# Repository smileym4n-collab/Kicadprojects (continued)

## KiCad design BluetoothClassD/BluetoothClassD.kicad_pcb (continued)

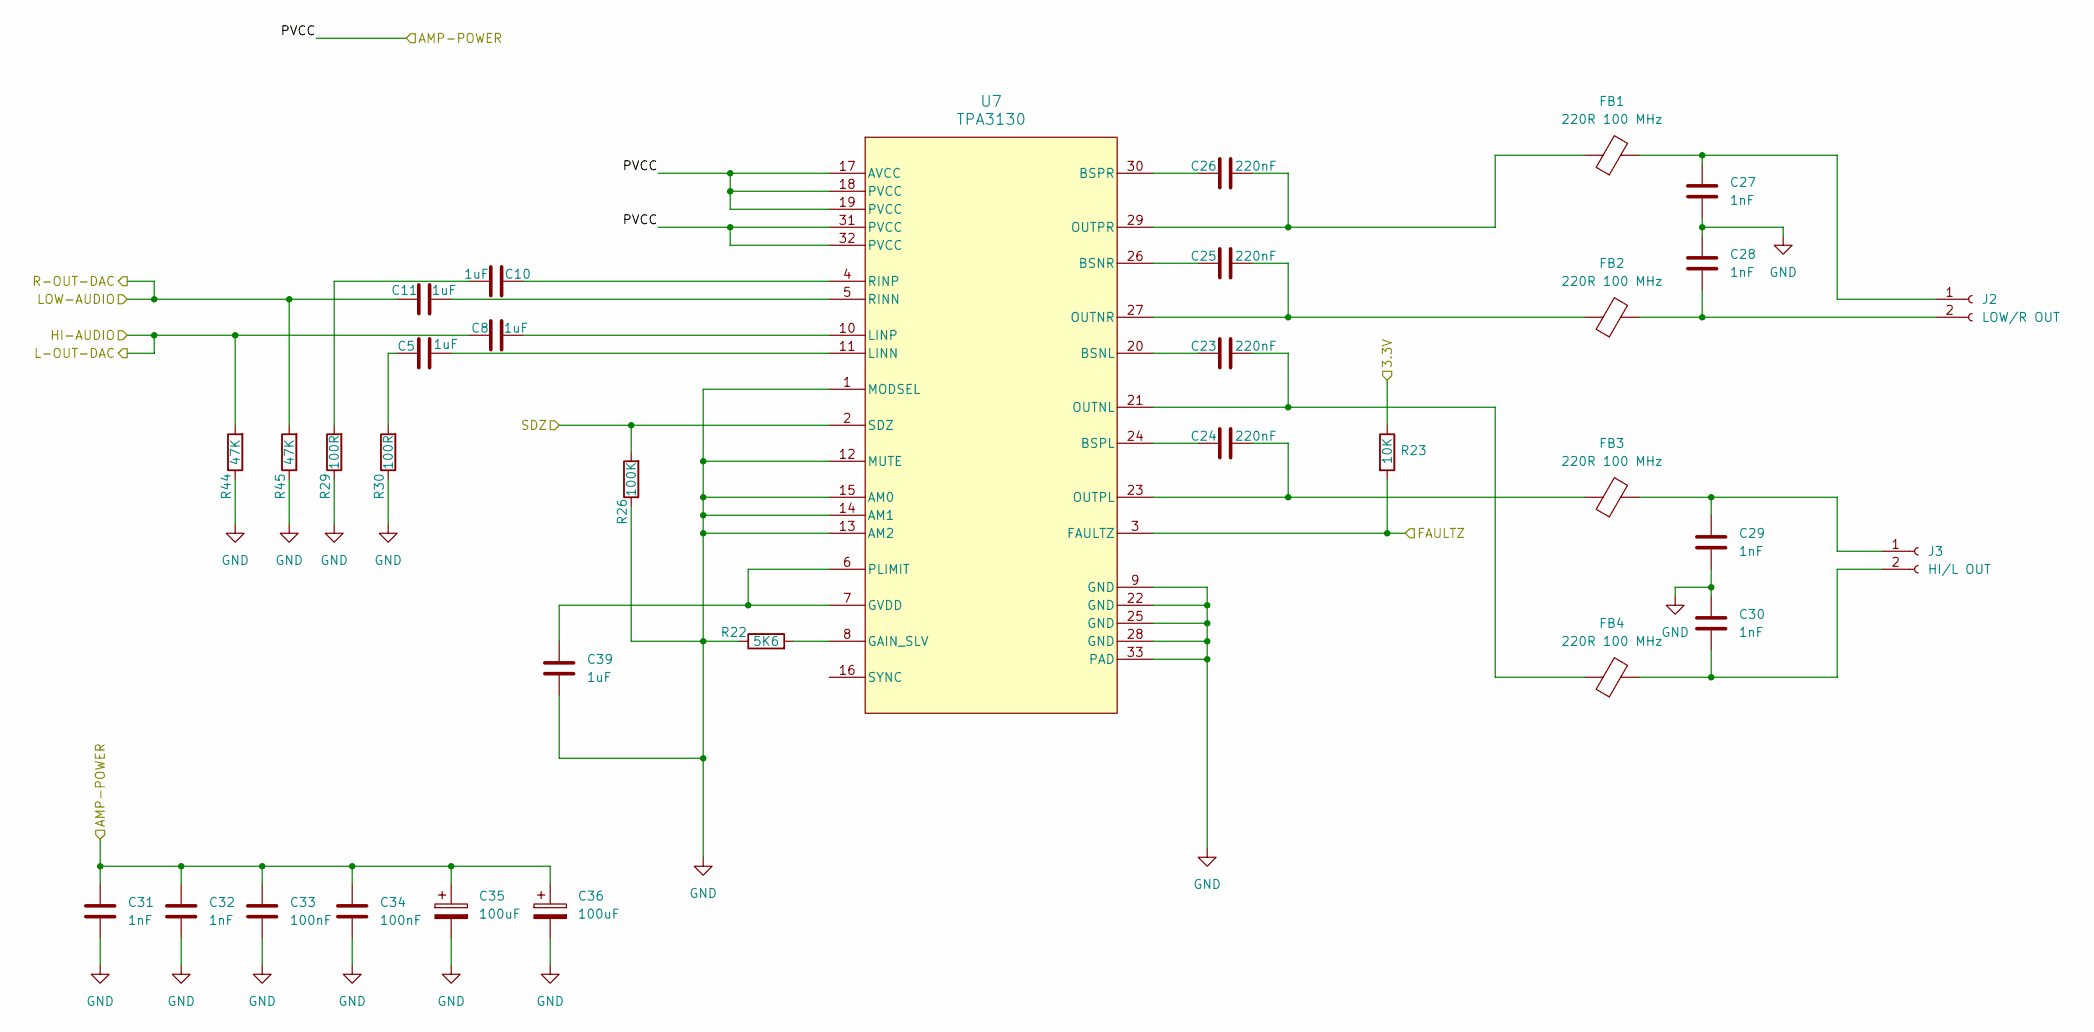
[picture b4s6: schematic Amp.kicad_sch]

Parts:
C5, C8, C10, C11: 1uF; C_Rect_L7.2mm_W5.5mm_P5.00mm_FKS2_FKP2_MKS2_MKP2
C23, C24, C25, C26: 220nF; C_0805_2012Metric_Pad1.18x1.45mm_HandSolder
C27, C28, C29, C30: 1nF; C_0805_2012Metric_Pad1.18x1.45mm_HandSolder
C31, C32: 1nF; C_0603_1608Metric_Pad1.08x0.95mm_HandSolder
C33, C34: 100nF; C_1206_3216Metric_Pad1.33x1.80mm_HandSolder
C35, C36: 100uF; CP_Radial_D8.0mm_P3.50mm
C39: 1uF; C_1206_3216Metric_Pad1.33x1.80mm_HandSolder
FB1, FB2, FB3, FB4: 220R 100 MHz; L_1206_3216Metric_Pad1.22x1.90mm_HandSolder
J2: LOW/R OUT; JST_XH_B2B-XH-A_1x02_P2.50mm_Vertical
J3: HI/L OUT; JST_XH_B2B-XH-A_1x02_P2.50mm_Vertical
R22: 5K6; R_0805_2012Metric_Pad1.20x1.40mm_HandSolder
R23: 10K; R_0805_2012Metric_Pad1.20x1.40mm_HandSolder
R26: 100K; R_0805_2012Metric_Pad1.20x1.40mm_HandSolder
R29, R30: 100R; R_0805_2012Metric_Pad1.20x1.40mm_HandSolder
R44, R45: 47K; R_0805_2012Metric_Pad1.20x1.40mm_HandSolder
U7: TPA3130; TPA3130D2DAPR

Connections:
/Amp/FAULTZ: R23.2, U7.3 (FAULTZ); also elsewhere on the board
/Amp/HI-AUDIO: C8.1, R44.2; also elsewhere on the board
/Amp/LOW-AUDIO: C11.1, R45.2; also elsewhere on the board
/Amp/PVCC: C31.1, C32.1, C33.1, C34.1, C35.1, C36.1, U7.17 (AVCC), U7.18 (PVCC), U7.19 (PVCC), U7.31 (PVCC), U7.32 (PVCC); also elsewhere on the board
/Amp/SDZ: R26.2, U7.2 (SDZ); also elsewhere on the board
/ESP-3V3: R23.1; also elsewhere on the board
GND: C27.2, C28.1, C29.2, C30.1, C31.2, C32.2, C33.2, C34.2, C35.2, C36.2, C39.2, R22.1, R26.1, R29.1, R30.1, R44.1, R45.1, U7.1 (MODSEL), U7.9 (GND), U7.12 (MUTE), U7.13 (AM2), U7.14 (AM1), U7.15 (AM0), U7.22 (GND), U7.25 (GND), U7.28 (GND), U7.33 (PAD); also elsewhere on the board
unnamed: C5.1, R30.2
unnamed: C10.1, R29.2
unnamed: C27.1, FB1.2, J2.1
unnamed: C28.2, FB2.2, J2.2
unnamed: C29.1, FB3.2, J3.1
unnamed: C30.2, FB4.2, J3.2
unnamed: C23.1, U7.20 (BSNL)
unnamed: C25.1, U7.26 (BSNR)
unnamed: C24.1, U7.24 (BSPL)
unnamed: C26.1, U7.30 (BSPR)
unnamed: R22.2, U7.8 (GAIN_SLV)
unnamed: C39.1, U7.6 (PLIMIT), U7.7 (GVDD)
unnamed: C5.2, U7.11 (LINN)
unnamed: C8.2, U7.10 (LINP)
unnamed: C23.2, FB4.1, U7.21 (OUTNL)
unnamed: C25.2, FB2.1, U7.27 (OUTNR)
unnamed: C24.2, FB3.1, U7.23 (OUTPL)
unnamed: C26.2, FB1.1, U7.29 (OUTPR)
unnamed: C11.2, U7.5 (RINN)
unnamed: C10.2, U7.4 (RINP)

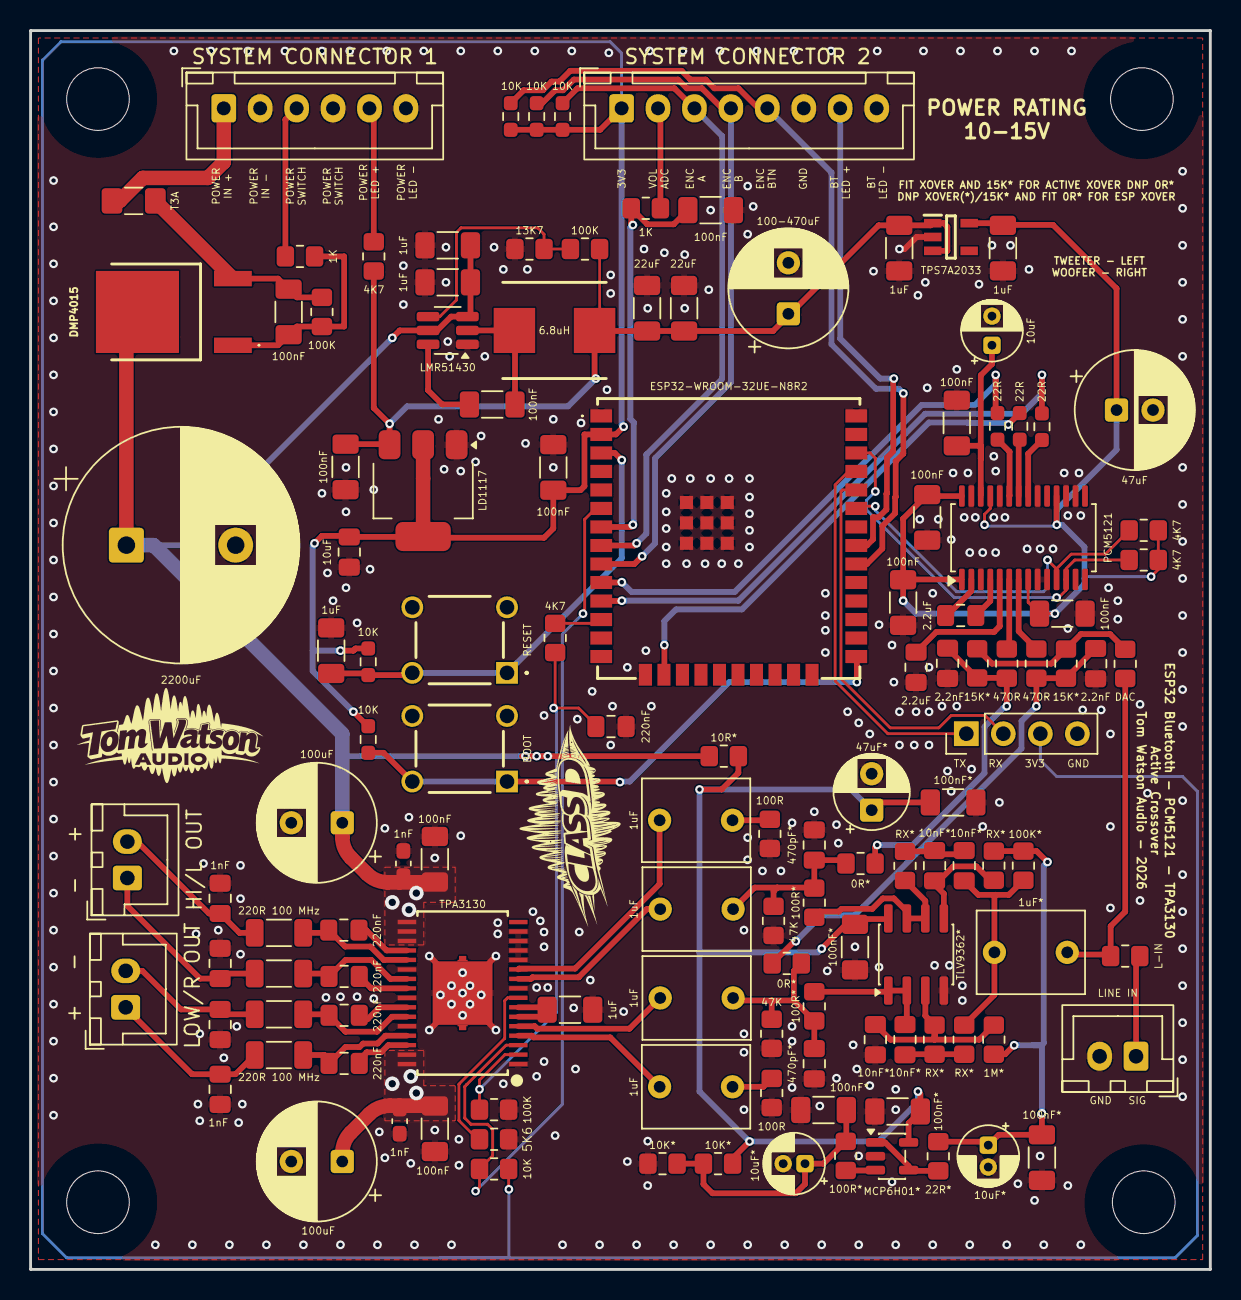
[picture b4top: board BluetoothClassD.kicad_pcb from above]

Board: 2 copper layers, 81.0 x 85.0 mm, 132 parts (0 on the bottom side), 79 nets.

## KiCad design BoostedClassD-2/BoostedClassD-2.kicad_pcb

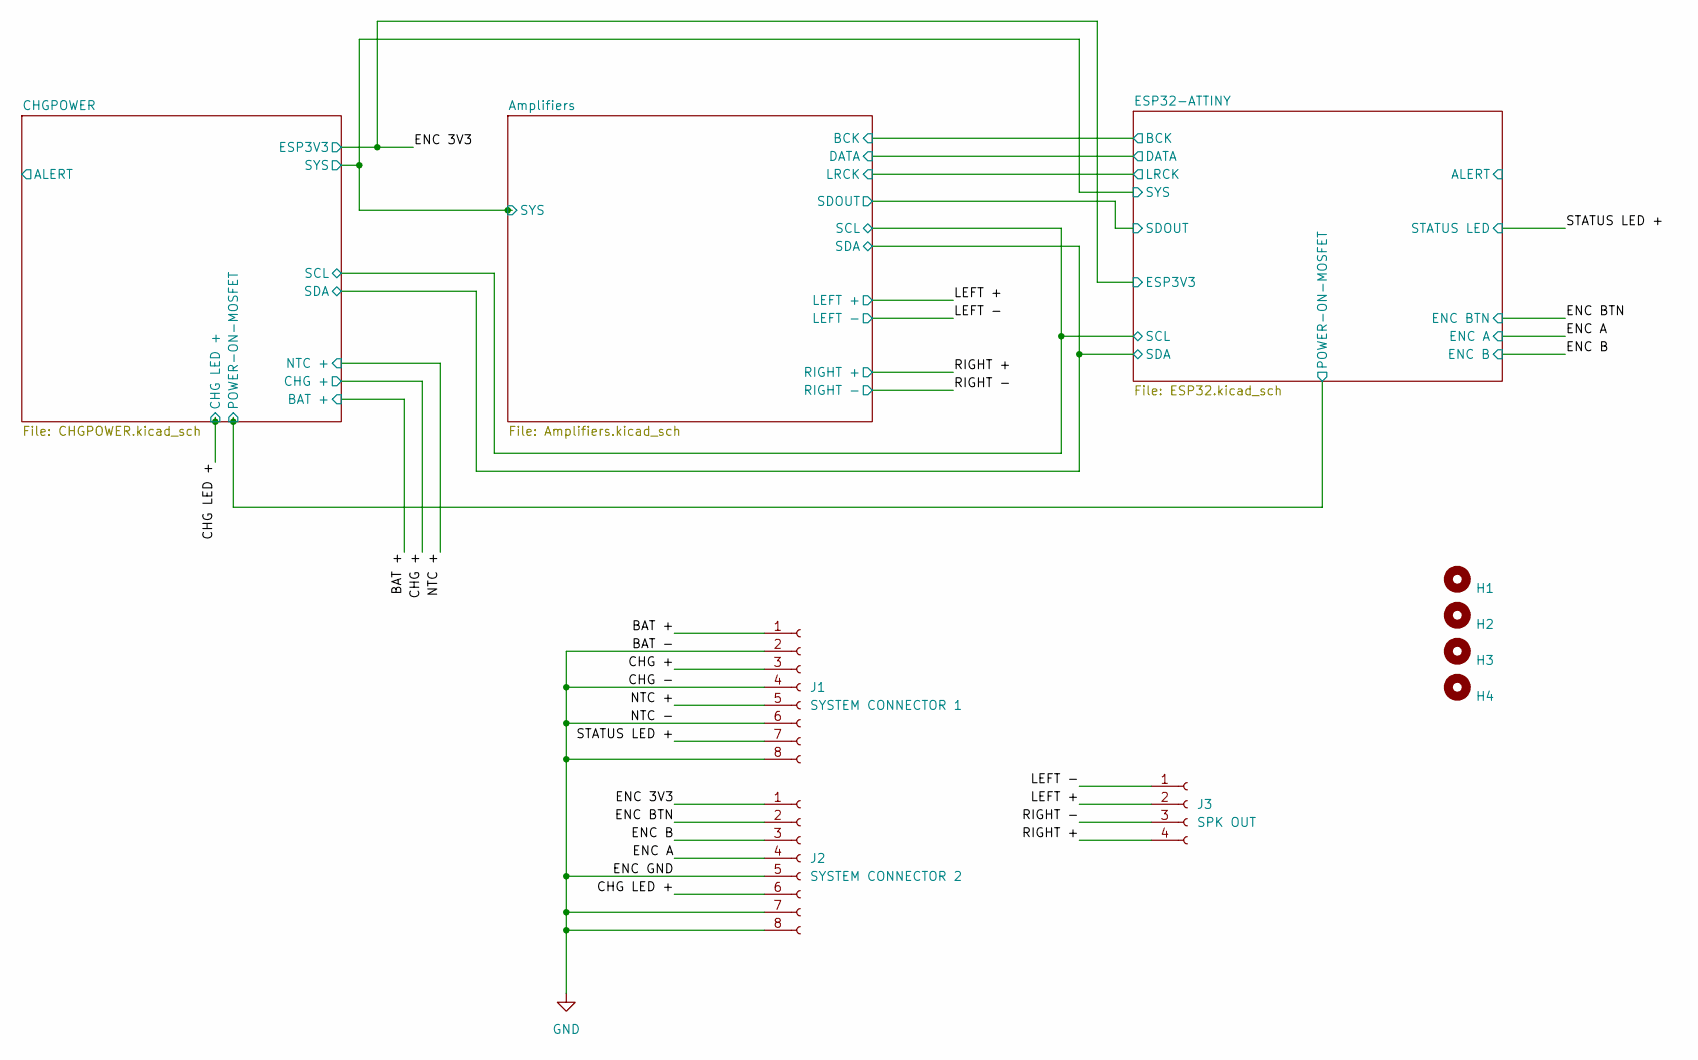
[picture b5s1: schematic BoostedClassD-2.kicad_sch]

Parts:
H1, H2, H3, H4: MountingHole_4.3mm_M4
J1: SYSTEM CONNECTOR 1; JST_XH_B8B-XH-A_1x08_P2.50mm_Vertical
J2: SYSTEM CONNECTOR 2; JST_XH_B8B-XH-A_1x08_P2.50mm_Vertical
J3: SPK OUT; JST_XH_B4B-XH-A_1x04_P2.50mm_Vertical

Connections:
/BAT +: J1.1; also elsewhere on the board
/CHG +: J1.3; also elsewhere on the board
/CHG LED +: J2.6; also elsewhere on the board
/ENC 3V3: J2.1; also elsewhere on the board
/ENC A: J2.4; also elsewhere on the board
/ENC B: J2.3; also elsewhere on the board
/ENC BTN: J2.2; also elsewhere on the board
/LEFT +: J3.2; also elsewhere on the board
/LEFT -: J3.1; also elsewhere on the board
/NTC +: J1.5; also elsewhere on the board
/RIGHT +: J3.4; also elsewhere on the board
/RIGHT -: J3.3; also elsewhere on the board
/STATUS LED +: J1.7; also elsewhere on the board
GND: J1.2, J1.4, J1.6, J1.8, J2.5, J2.7, J2.8; also elsewhere on the board

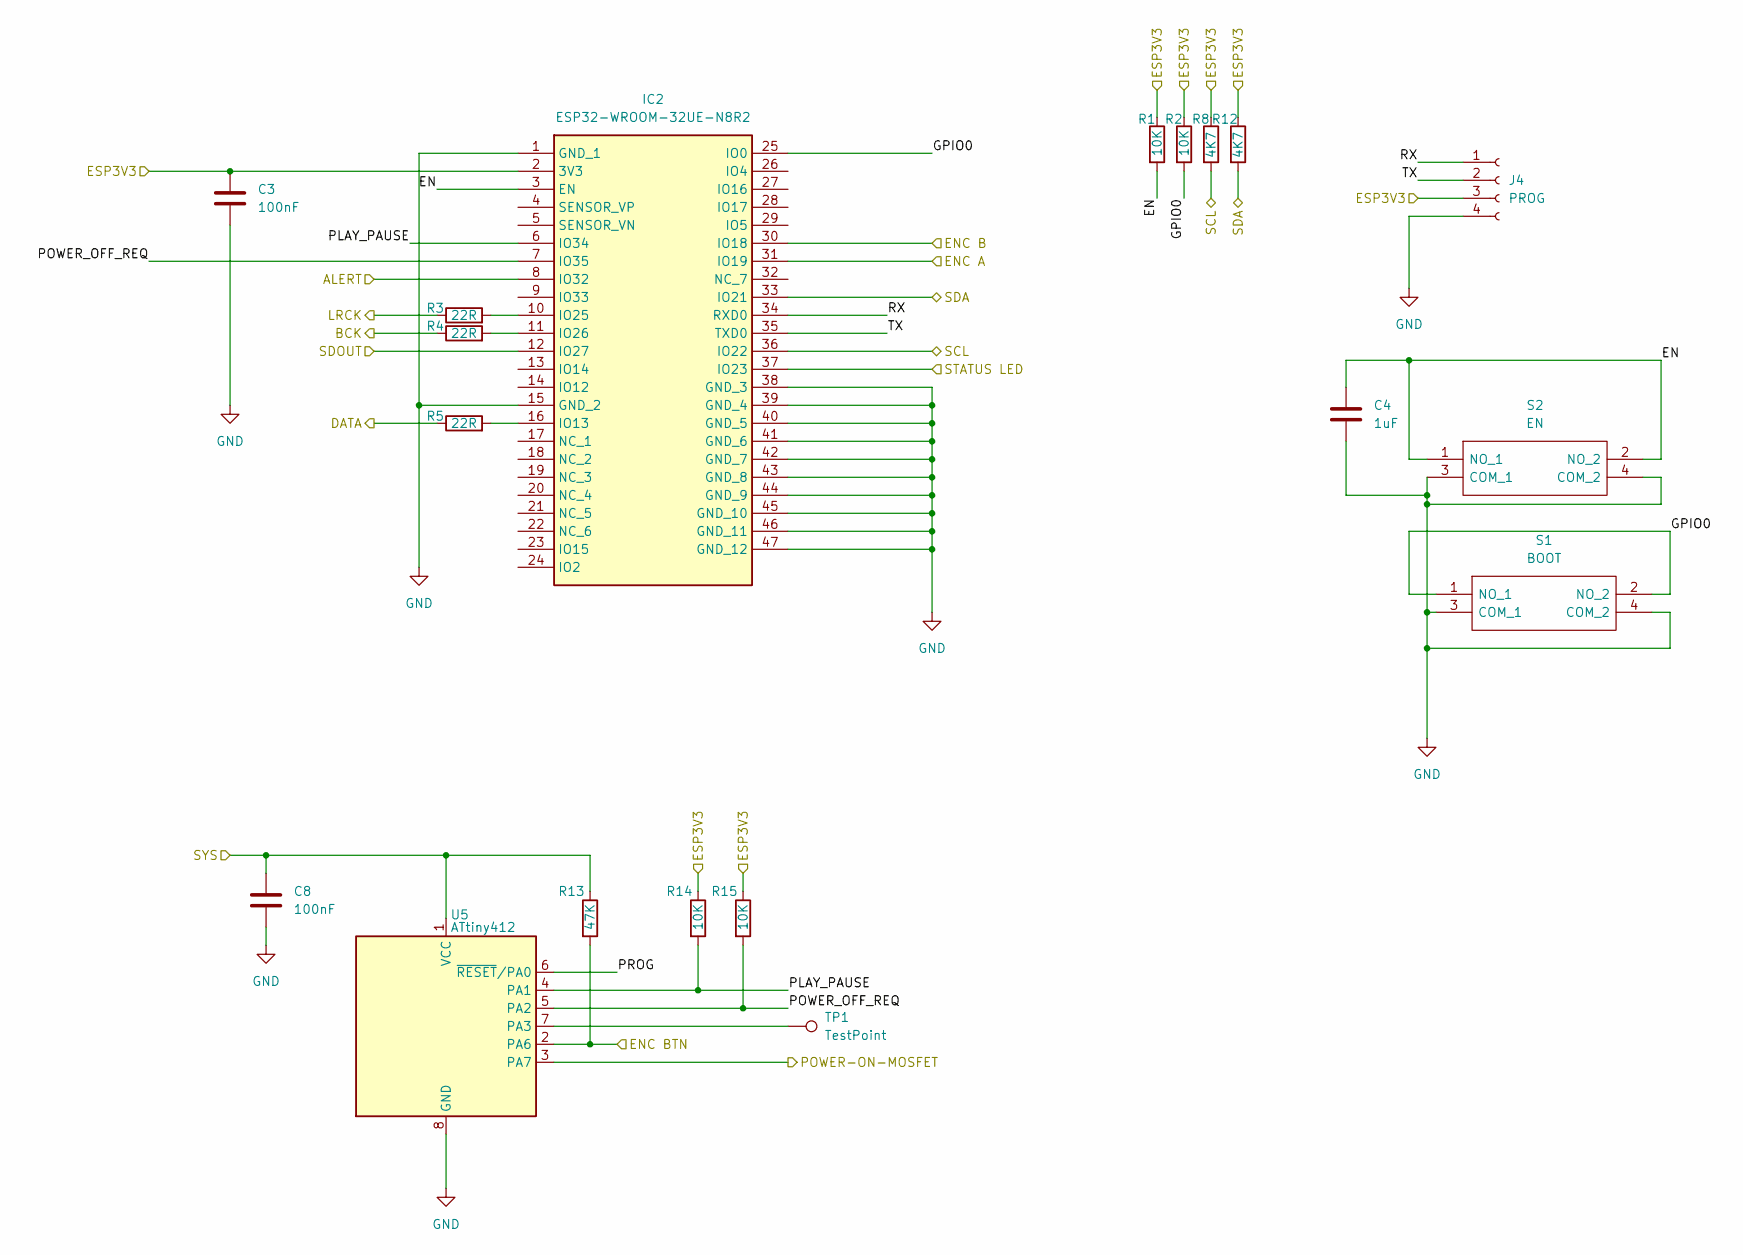
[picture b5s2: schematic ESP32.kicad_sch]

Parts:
C3, C8: 100nF; C_1206_3216Metric_Pad1.33x1.80mm_HandSolder
C4: 1uF; C_1206_3216Metric_Pad1.33x1.80mm_HandSolder
IC2: ESP32-WROOM-32UE-N8R2; ESP32WROOM32UEN8R2; Mouser Part Number 356-ESP32WRM32UEN8R2
J4: PROG; PinHeader_1x04_P2.54mm_Vertical
R1, R2: 10K; R_0603_1608Metric_Pad0.98x0.95mm_HandSolder
R3, R4, R5: 22R; R_0603_1608Metric_Pad0.98x0.95mm_HandSolder
R8, R12: 4K7; R_0805_2012Metric_Pad1.20x1.40mm_HandSolder
R13: 47K; R_0805_2012Metric_Pad1.20x1.40mm_HandSolder
R14, R15: 10K; R_0805_2012Metric_Pad1.20x1.40mm_HandSolder
S1: BOOT; PTS810SJM250SMTRLFS; Mouser Part Number 611-PTS810SJM250SMTR
S2: EN; PTS810SJM250SMTRLFS; Mouser Part Number 611-PTS810SJM250SMTR
TP1: TestPoint; TestPoint_Pad_D2.0mm
U5: ATtiny412; SOIC-8_3.9x4.9mm_P1.27mm

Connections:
/Amplifiers/BCK: R4.1; also elsewhere on the board
/Amplifiers/DATA: R5.1; also elsewhere on the board
/Amplifiers/LRCK: R3.1; also elsewhere on the board
/Amplifiers/SCL: IC2.36 (IO22), R8.2; also elsewhere on the board
/Amplifiers/SDA: IC2.33 (IO21), R12.2; also elsewhere on the board
/Amplifiers/SDOUT: IC2.12 (IO27)
/Amplifiers/SYS: C8.1, R13.1, U5.1 (VCC); also elsewhere on the board
/CHGPOWER/POWER-ON-MOSFET: U5.3 (PA7); also elsewhere on the board
/ENC 3V3: C3.1, IC2.2 (3V3), J4.3, R1.1, R2.1, R8.1, R12.1, R14.1, R15.1; also elsewhere on the board
/ENC A: IC2.31 (IO19); also elsewhere on the board
/ENC B: IC2.30 (IO18); also elsewhere on the board
/ENC BTN: R13.2, U5.2 (PA6); also elsewhere on the board
/ESP32-ATTINY/ALERT: IC2.8 (IO32)
/ESP32-ATTINY/EN: C4.1, IC2.3 (EN), R1.2, S2.1 (NO_1), S2.2 (NO_2)
/ESP32-ATTINY/GPIO0: IC2.25 (IO0), R2.2, S1.1 (NO_1), S1.2 (NO_2)
/ESP32-ATTINY/PLAY_PAUSE: IC2.6 (IO34), R14.2, U5.4 (PA1)
/ESP32-ATTINY/POWER_OFF_REQ: IC2.7 (IO35), R15.2, U5.5 (PA2)
/ESP32-ATTINY/PROG: U5.6 (~RESET/PA0)
/ESP32-ATTINY/RX: IC2.34 (RXD0), J4.1
/ESP32-ATTINY/TX: IC2.35 (TXD0), J4.2
/STATUS LED +: IC2.37 (IO23); also elsewhere on the board
GND: C3.2, C4.2, C8.2, IC2.1 (GND_1), IC2.15 (GND_2), IC2.38 (GND_3), IC2.39 (GND_4), IC2.40 (GND_5), IC2.41 (GND_6), IC2.42 (GND_7), IC2.43 (GND_8), IC2.44 (GND_9), IC2.45 (GND_10), IC2.46 (GND_11), IC2.47 (GND_12), J4.4, S1.3 (COM_1), S1.4 (COM_2), S2.3 (COM_1), S2.4 (COM_2), U5.8 (GND); also elsewhere on the board
unnamed: IC2.16 (IO13), R5.2
unnamed: IC2.10 (IO25), R3.2
unnamed: IC2.11 (IO26), R4.2
unnamed: TP1.1 (1_1), U5.7 (PA3)

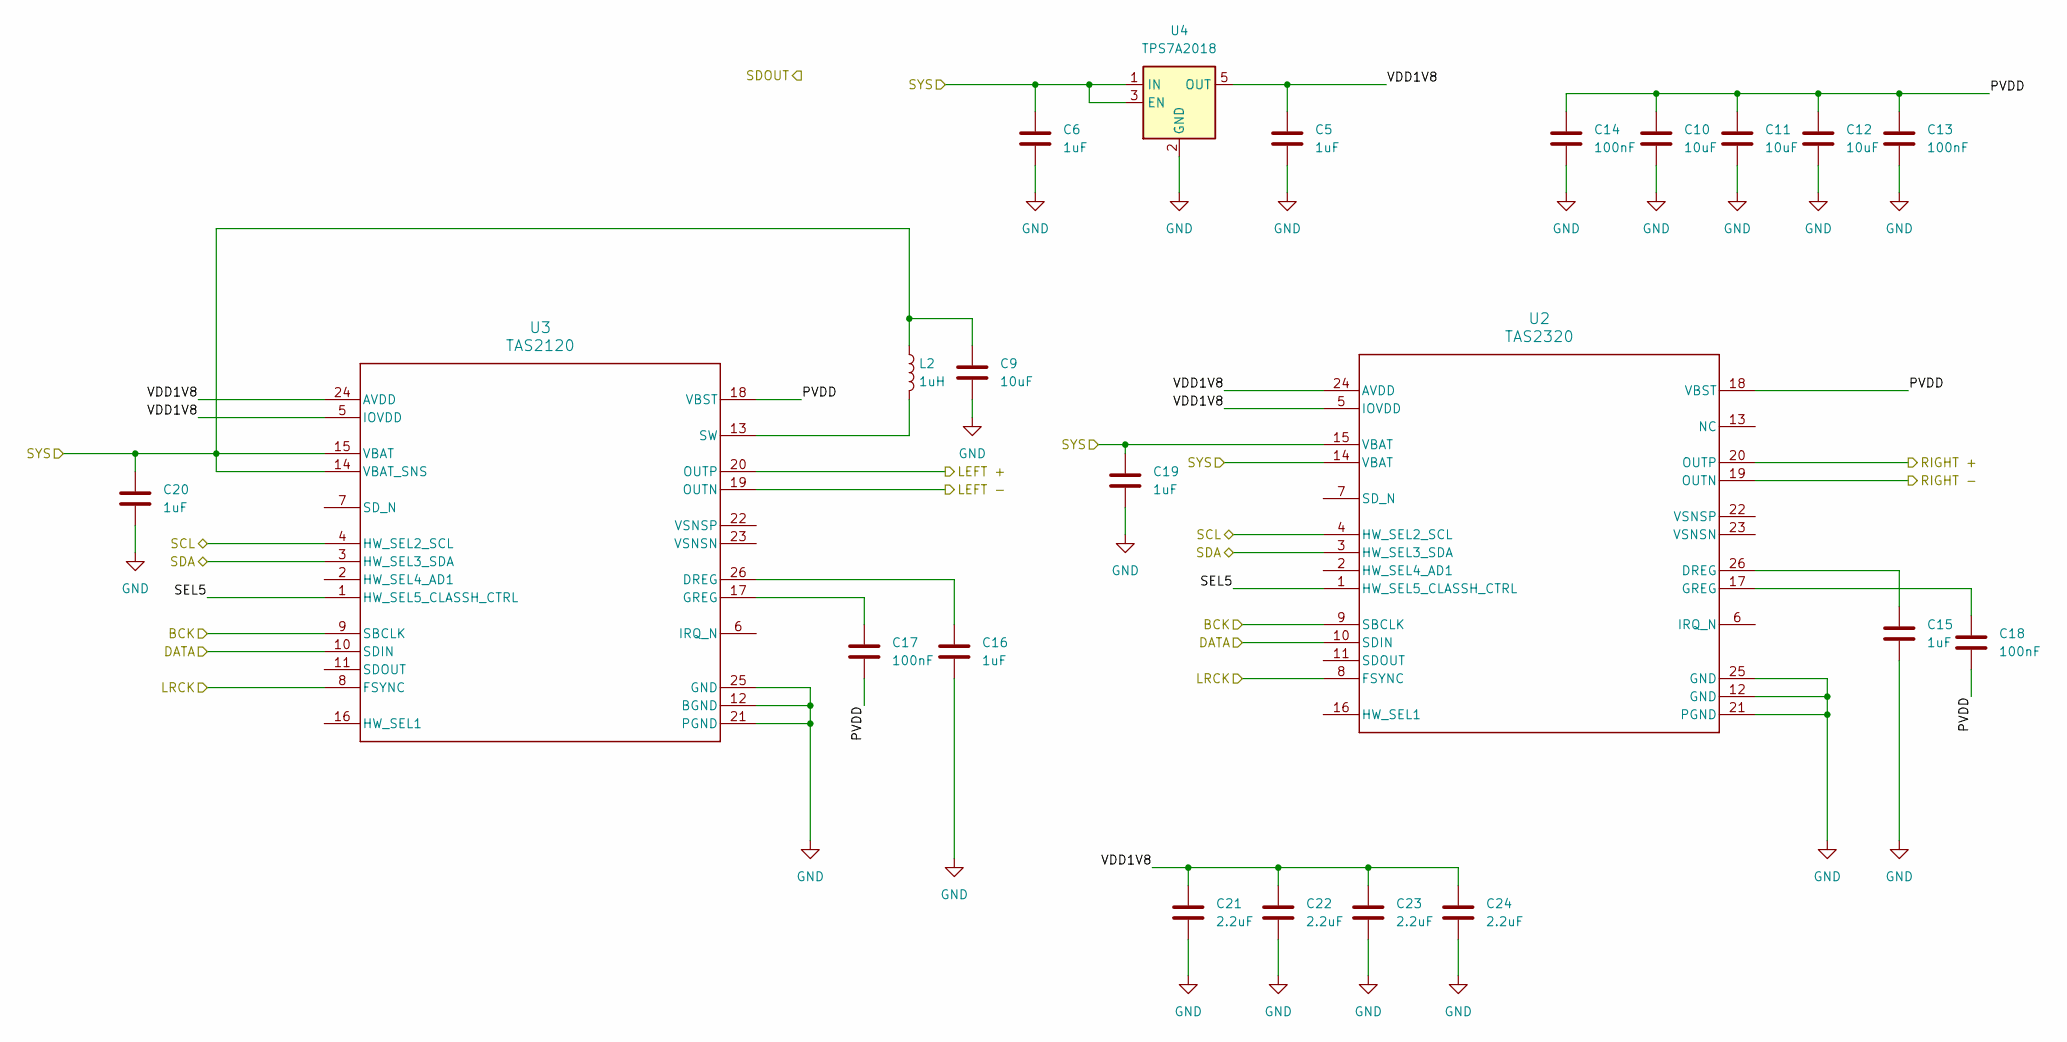
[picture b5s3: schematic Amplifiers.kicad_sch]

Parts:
C5, C6, C15, C16, C19, C20: 1uF; C_1206_3216Metric_Pad1.33x1.80mm_HandSolder
C9, C10, C11, C12: 10uF; C_1206_3216Metric_Pad1.33x1.80mm_HandSolder
C13, C14, C17, C18: 100nF; C_1206_3216Metric_Pad1.33x1.80mm_HandSolder
C21, C22, C23, C24: 2.2uF; C_0805_2012Metric_Pad1.18x1.45mm_HandSolder
L2: 1uH; L_1008_2520Metric_Pad1.43x2.20mm_HandSolder
U2: TAS2320; TAS2120
U3: TAS2120
U4: TPS7A2018; SOT-23-5

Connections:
/Amplifiers/BCK: U2.9 (SBCLK), U3.9 (SBCLK); also elsewhere on the board
/Amplifiers/DATA: U2.10 (SDIN), U3.10 (SDIN); also elsewhere on the board
/Amplifiers/LRCK: U2.8 (FSYNC), U3.8 (FSYNC); also elsewhere on the board
/Amplifiers/PVDD: C10.1, C11.1, C12.1, C13.1, C14.1, C17.2, C18.2, U2.18 (VBST), U3.18 (VBST)
/Amplifiers/SCL: U2.4 (HW_SEL2_SCL), U3.4 (HW_SEL2_SCL); also elsewhere on the board
/Amplifiers/SDA: U2.3 (HW_SEL3_SDA), U3.3 (HW_SEL3_SDA); also elsewhere on the board
/Amplifiers/SEL5: U2.1 (HW_SEL5_CLASSH_CTRL), U3.1 (HW_SEL5_CLASSH_CTRL)
/Amplifiers/SYS: C6.1, C9.1, C19.1, C20.1, L2.1, U2.14 (VBAT), U2.15 (VBAT), U3.14 (VBAT_SNS), U3.15 (VBAT), U4.1 (IN), U4.3 (EN); also elsewhere on the board
/Amplifiers/VDD1V8: C5.1, C21.1, C22.1, C23.1, C24.1, U2.5 (IOVDD), U2.24 (AVDD), U3.5 (IOVDD), U3.24 (AVDD), U4.5 (OUT)
/LEFT +: U3.20 (OUTP); also elsewhere on the board
/LEFT -: U3.19 (OUTN); also elsewhere on the board
/RIGHT +: U2.20 (OUTP); also elsewhere on the board
/RIGHT -: U2.19 (OUTN); also elsewhere on the board
GND: C5.2, C6.2, C9.2, C10.2, C11.2, C12.2, C13.2, C14.2, C15.2, C16.2, C19.2, C20.2, C21.2, C22.2, C23.2, C24.2, U2.12 (GND), U2.21 (PGND), U2.25 (GND), U3.12 (BGND), U3.21 (PGND), U3.25 (GND), U4.2 (GND); also elsewhere on the board
unnamed: C15.1, U2.26 (DREG)
unnamed: C18.1, U2.17 (GREG)
unnamed: C16.1, U3.26 (DREG)
unnamed: C17.1, U3.17 (GREG)
unnamed: L2.2, U3.13 (SW)

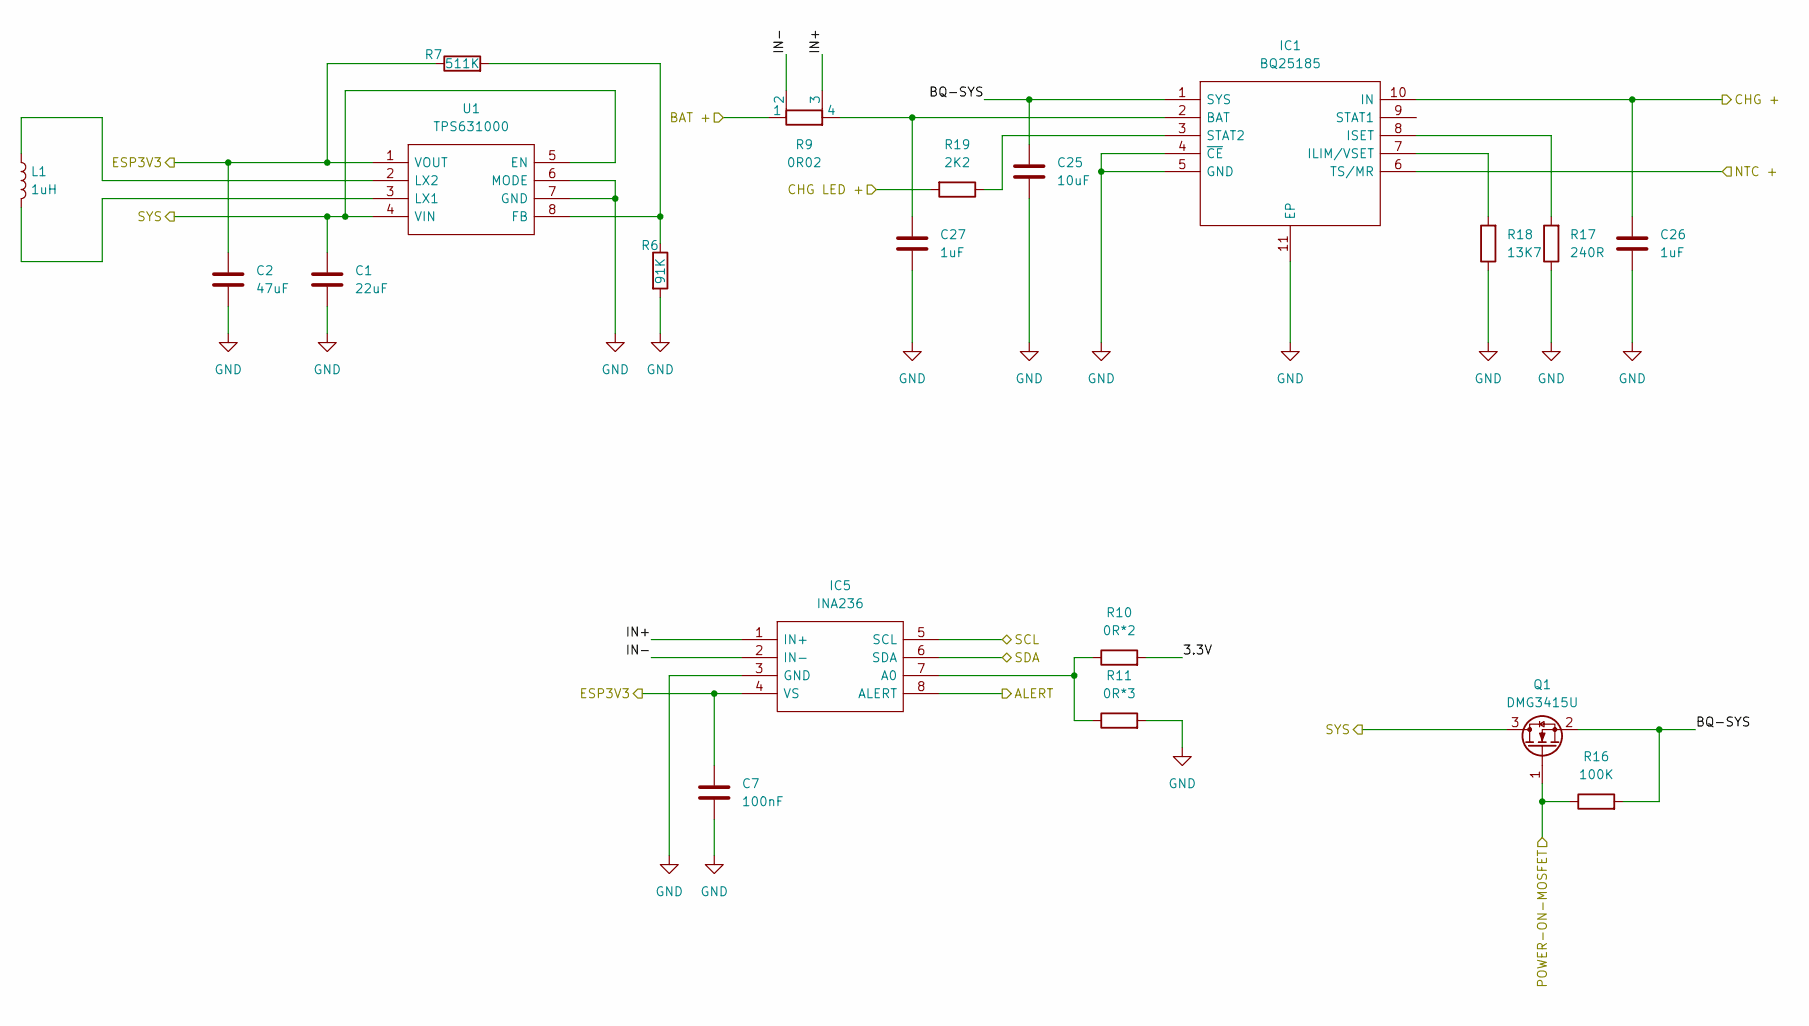
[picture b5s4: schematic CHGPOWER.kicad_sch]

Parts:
C1: 22uF; C_0805_2012Metric_Pad1.18x1.45mm_HandSolder
C2: 47uF; C_0805_2012Metric_Pad1.18x1.45mm_HandSolder
C7: 100nF; C_1206_3216Metric_Pad1.33x1.80mm_HandSolder
C25: 10uF; C_1206_3216Metric_Pad1.33x1.80mm_HandSolder
C26, C27: 1uF; C_1206_3216Metric_Pad1.33x1.80mm_HandSolder
IC1: BQ25185; BQ25185DLHR; Mouser Part Number 595-BQ25185DLHR
IC5: INA236; INA236BIDDFR; Mouser Part Number 595-INA236BIDDFR
L1: 1uH; L_1008_2520Metric_Pad1.43x2.20mm_HandSolder
Q1: DMG3415U; SOT-23
R6: 91K; R_0805_2012Metric_Pad1.20x1.40mm_HandSolder
R7: 511K; R_0805_2012Metric_Pad1.20x1.40mm_HandSolder
R9: 0R02; Untitled_4
R10: 0R*2; R_0805_2012Metric_Pad1.20x1.40mm_HandSolder
R11: 0R*3; R_0805_2012Metric_Pad1.20x1.40mm_HandSolder
R16: 100K; R_0805_2012Metric_Pad1.20x1.40mm_HandSolder
R17: 240R; R_0805_2012Metric_Pad1.20x1.40mm_HandSolder
R18: 13K7; R_0805_2012Metric_Pad1.20x1.40mm_HandSolder
R19: 2K2; R_0805_2012Metric_Pad1.20x1.40mm_HandSolder
U1: TPS631000; Mouser Part Number 595-TPS631000DRLR

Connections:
/Amplifiers/SCL: IC5.5 (SCL); also elsewhere on the board
/Amplifiers/SDA: IC5.6 (SDA); also elsewhere on the board
/Amplifiers/SYS: C1.1, Q1.3 (D), U1.4 (VIN), U1.5 (EN); also elsewhere on the board
/BAT +: R9.1; also elsewhere on the board
/CHG +: C26.1, IC1.10 (IN); also elsewhere on the board
/CHG LED +: R19.2; also elsewhere on the board
/CHGPOWER/3.3V: R10.2
/CHGPOWER/ALERT: IC5.8 (ALERT)
/CHGPOWER/BQ-SYS: C25.1, IC1.1 (SYS), Q1.2 (S), R16.2
/CHGPOWER/IN+: IC5.1 (IN+), R9.3
/CHGPOWER/IN-: IC5.2 (IN-), R9.2
/CHGPOWER/POWER-ON-MOSFET: Q1.1 (G), R16.1; also elsewhere on the board
/ENC 3V3: C2.1, C7.1, IC5.4 (VS), R7.1, U1.1 (VOUT); also elsewhere on the board
/NTC +: IC1.6 (TS/MR); also elsewhere on the board
GND: C1.2, C2.2, C7.2, C25.2, C26.2, C27.2, IC1.4 (~CE), IC1.5 (GND), IC1.11 (EP), IC5.3 (GND), R6.2, R11.2, R17.1, R18.1, U1.6 (MODE), U1.7 (GND); also elsewhere on the board
unnamed: C27.1, IC1.2 (BAT), R9.4
unnamed: IC1.7 (ILIM/VSET), R18.2
unnamed: IC1.8 (ISET), R17.2
unnamed: IC1.3 (STAT2), R19.1
unnamed: IC5.7 (A0), R10.1, R11.1
unnamed: R6.1, R7.2, U1.8 (FB)
unnamed: L1.2, U1.3 (LX1)
unnamed: L1.1, U1.2 (LX2)

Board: 4 copper layers, 68 parts (0 on the bottom side), 50 nets, no tracks yet.

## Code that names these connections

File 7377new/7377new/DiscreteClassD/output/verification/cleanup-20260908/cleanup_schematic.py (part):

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 for r,x in [('C29',30),('C30',40)]:
  s.place(r,x,84);s.w(s.pp(r,1),(x,77));s.groundpin(r,2)
 s.w((18,77),(50,77));s.place('U3',53,78,unit=1);s.w((50,77),s.pp('U3',3))
 s.w(s.pp('U3',1),(61,78),(61,90),(47,90),(47,79),s.pp('U3',2));s.label('VREF_2V5',(61,78));s.tp('TP21',61,74,(61,78))
 s.title('3. SHARED 400 kHz OSCILLATOR',82,60)
 s.place('U7',112,78,unit=1);s.place('R26',94,77,90);s.place('R27',110,66,270)
 s.w((84,77),s.pp('R26',1));s.label('TRIANGLE_400K',(84,77),right=True)
 s.w(s.pp('R26',2),(103,77),s.pp('U7',1));s.w(s.pp('R27',1),(120,66),(120,78),s.pp('U7',7))
 s.w(s.pp('R27',2),(103,66),(103,77));s.w(s.pp('U7',2),(106,79));s.label('VREF_2V5',(106,79),right=True)
 # R27 pin 1 must be comparator OUT, pin 2 SUM: resistor is nonpolar; preserve numbering by rotation.
 # Reverse its orientation, then rewire its endpoints explicitly below during final topology check.
 s.place('R28',136,78,90);s.w((120,78),s.pp('R28',1));s.label('OSC_SQUARE',(122,78));s.tp('TP22',125,74,(125,78))
 s.place('U3',158,77,unit=2);s.w(s.pp('R28',2),(147,78),s.pp('U3',6,2));s.w(s.pp('U3',5,2),(151,76));s.label('VREF_2V5',(151,76),right=True)
 s.place('C31',158,66,90);s.w(s.pp('C31',1),(147,66),(147,78));s.w(s.pp('C31',2),(167,66),(167,77),s.pp('U3',7,2));s.label('TRIANGLE_400K',(167,77));s.tp('TP23',174,74,(174,77));s.w((167,77),(174,77))
 s.text('Non-inverting Schmitt + inverting integrator\n49.9k / 10k; 3.09k x 1nF: nominal 403.72 kHz\nTriangle approx. 1.999 to 3.001 V. Measure / tune.',91,91,1.15)
def powerunit(s,ref,idunit,x,y,vp,vm,rail,caps):
 s.place(ref,x,y,unit=idunit);pp=s.pp(ref,vp,idunit);top=y-6
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 rn,rp,dp,dn,capP,capN=('R33','R32','D20','D21','C42','C43') if isL else ('R40','R39','D22','D23','C47','C48')
 s.title(('4. LEFT' if isL else '5. RIGHT')+' INPUT / PWM / DEAD TIME',10,y-14)
 s.place(cin,21,y,90);s.place(rf,36,y,90);prop(s.comps[(rf,1)],'Value')[2]=Q('51k')
 s.w((12,y),s.pp(cin,1));s.label('LEFT_IN' if isL else 'RIGHT_IN',(12,y),right=True);s.join(cin,2,rf,1)
 s.place('U1',65,y+1,unit=ou);pnplus,pnminus,pnout=('3','2','1') if isL else ('5','6','7')
 s.w(s.pp(rf,2),s.pp('U1',pnplus,ou))
 for r,x in [(rt,45),(cr,54)]:s.place(r,x,y+10);s.w((x,y),s.pp(r,1));s.w(s.pp(r,2),(x,y+15))
 s.w((45,y+15),(54,y+15));s.label('VREF_2V5',(45,y+15),right=True)
 s.w(s.pp('U1',pnout,ou),(73,y+1),(73,y+13),(59,y+13),(59,y+2),s.pp('U1',pnminus,ou))
 s.place(ri,81,y+1,90);s.w((73,y+1),s.pp(ri,1));s.place(cmp,105,y+2,unit=cu)
 plus,minus,out=('4','3','6') if isL else ('1','2','7');s.w(s.pp(ri,2),s.pp(cmp,plus,cu));s.label('AUDIO_'+ch,(88,y+1));s.tp(tpa,91,y-3,(91,y+1))
 s.w(s.pp(cmp,minus,cu),(98,y+3));s.label('TRIANGLE_400K',(98,y+3),right=True)
 s.w(s.pp(cmp,out,cu),(125,y+2),(125,y));s.label('PWM_'+ch,(115,y+2));s.tp(tpp,119,y-2,(119,y+2))
 # Two complete RC/diode/Schmitt paths, directly wired.
 for unit,yy,r,d,c,tpn in [(1,y,rp,dp,capP,tppos),(2,y+23,rn,dn,capN,tpneg)]:
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 shared(s)
 s.title('IC SUPPLY PINS / LOCAL BYPASS',10,96)
 for args in [('U1',3,18,106,'8','4','+12V_A',['C32','C33']),('U3',3,61,106,'8','4','+12V_A',['C34','C35']),('U7',3,108,106,'8','5','+5V_A',['C36']),('U8',3,145,106,'8','5','+5V_A',['C37']),('U5',3,187,106,'5','2','+5V_A',['C38']),('U10',3,228,106,'5','2','+5V_A',['C39'])]:powerunit(s,*args)
 s.place('U8',280,77,unit=2);s.w(s.pp('U8',4,2),(270,76),(270,73));s.gnd((270,73));s.w(s.pp('U8',3,2),(272,78));s.label('VREF_2V5',(272,78),right=True);s.nc('U8',6,2);s.text('U8B spare: stable LOW after VREF settles.',259,89,1.2)
 s.place('J1',238,70);s.w(s.pp('J1',1),(232,69),(232,65));s.label('LEFT_IN',(232,65),right=True);s.w(s.pp('J1',3),(234,71),(234,76));s.label('RIGHT_IN',(234,76));s.w(s.pp('J1',2),(226,70),(226,73));s.gnd((226,73))
 channel(s,'L',131);channel(s,'R',180)
 # A1 provides room for conventional local wiring without reducing symbol scale.
 s.text('Input attenuation = 10k / (51k + 10k) = 0.163934; 2 Vrms -> 0.32787 Vrms / 0.463677 Vpk.\nOne board-wide GND. BTL speaker terminals remain floating. OPA1656 supply: filtered +12V_A.',10,225,1.2)
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 s.place(rr('C15'),94,99);s.place(rr('R15'),108,96);s.place(rr('C16'),108,103);s.place(rr('J15'),117,98)
 s.w(s.pp(rr('L6'),2),(112,93),(112,98),s.pp(rr('J15'),1));s.w(s.pp(rr('L6'),3),(86,95),(86,107),(114,107),(114,99),s.pp(rr('J15'),2))
 s.w((94,93),s.pp(rr('C15'),1));s.w(s.pp(rr('C15'),2),(94,107));s.w((108,93),s.pp(rr('R15'),1));s.join(rr('R15'),2,rr('C16'),1);s.w(s.pp(rr('C16'),2),(108,107))
 s.label('OUT_A',(88,93));s.label('OUT_B',(88,107));s.tp(rr('TP7'),92,90,(92,93));s.tp(rr('TP8'),88,104,(88,107))
 for r,net,x in [(rr('C18'),'OUT_A',44),(rr('C19'),'OUT_B',57)]:
  s.place(r,x,103);s.w(s.pp(r,1),(x,98));s.label(net,(x,98));s.groundpin(r,2)
 s.text('DNP output capacitors retained.\nNeither speaker terminal is grounded.',5,108,1.05)
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
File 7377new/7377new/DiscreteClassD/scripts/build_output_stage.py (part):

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text_('DIFFERENTIAL OUTPUT / 8 OHM SPEAKER',20.32,207.01,1.8)
add('Device:L_Coupled_1243','L6','CSAD0660-100M',55.88,231.14,foot='DiscreteClassD:CSAD0660-100M',old='L6',extra={'Datasheet':'https://www.codaca.com/Private/pdf/CSAD0660.pdf','Inductance':'2 x 10uH','Verification':'Verified: Codaca CSAD0660.pdf page 1, revised 2020-07-14; windings 1-2 and 4-3'})
for pn,yy in [('Reference',219.71),('Value',222.25)]:get(prop(comps['L6'],pn),'at')[1:]=['55.88',str(yy),'0']
for n,net in [('1','SW_A'),('2','OUT_A'),('4','SW_B'),('3','OUT_B')]:netpin('L6',n,net,dx=-10.16 if n in ['1','4'] else 10.16)
add('Device:C','C15','330n',93.98,231.14,foot='Capacitor_SMD:C_2220_5750Metric',extra={'Voltage':'100V','Dielectric':'Low-loss C0G / SMD film only','Requirement':'Provisional 5750 metric land pattern; exact stock/parallel realization and ripple rating to be selected'})
two('C15','OUT_A','OUT_B')
add('Device:R','R15','10R / 1W',129.54,220.98,foot='Resistor_SMD:R_2512_6332Metric',extra={'Requirement':'Non-inductive; verify heating at switching residual and full output'})
add('Device:C','C16','100n / 100V',129.54,238.76,foot='Capacitor_SMD:C_1210_3225Metric',extra={'Dielectric':'C0G or SMD film','Requirement':'Exact low-loss part to be selected'})
netpin('R15','1','OUT_A',dy=-2.54);wire(pins('R15')['2'],pins('C16')['1']);netpin('C16','2','OUT_B',dy=2.54);intended['R15']['2']='ZOBEL';intended['C16']['1']='ZOBEL'
add('Connector:Conn_01x02_Socket','J15','SPEAKER OUT',160.02,228.6,foot='DiscreteClassD:Power_Input_2_SMD',old='J15')
netpin('J15','1','OUT_A',dx=-5.08);netpin('J15','2','OUT_B',dx=-5.08)
text_('Speaker floats: neither terminal connects to PGND.\nL6: 10uH per winding; verified pins 1-2 and 4-3.',20.32,250.19,1.05)
for net,xx in [('OUT_A',50.8),('OUT_B',88.9)]:tp(net,xx,266.7)
# Input supplies and bulk
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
